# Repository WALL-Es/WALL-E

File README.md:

# WALL-E
-----------------------

----------------

## Description
A Full size Wall-E Clone from the movie WALL-E. With a ROS2+Gazebo Simulation. With Full CAD designs. 

## Featrues:
1. It will have a Simulation made with Gazebo.
2. Emulating the full motion of the real WALL-E.
3. Full PCB & 3D CAD designs.
4. Real Wall-E size.

### In V2:
- Autonomous motion
    - Adabting the Simulation using ROS2 Sensors
- Voice commanding & Sound system

## Photos:

### PCB:

### Schematic (See the [PDF](PCB/Schematic.pdf))
### 3D: 

### Simulation Demo:

https://github.com/user-attachments/assets/cbfe52af-3437-4783-bf1c-e89359c1bae6

## How to Build:

### 3D CAD:
1. Clone the Repo.
2. In the SW(Pack&Go) Directory, take the Wall-E.zip file and unzip it.
3. Open the main assembly in SolidWorks.
4. Edit whatever you want.
5. You can from there export to any format.
6. Enjoy.

### PCB:
1. Clone the Repo.
2. Open the PCB folder in Kicad.
3. Edit whateve you want.
4. That's it, Enjoy.

### Simulation:
1. Clone the Wall-E_Simulation Repo (You will find a shortcut in the GZ_simulation folder)
2. Make sure you have ROS2 Lyrical (Or any ROS2 Distro I believe) & Gazebo_Sim not Classic, installed on your linux machine.
3. Copy the package folder to your ROS2 Workspace.
4. Run `colcon build` and don't forget to source your workspace
5. Edit whatever you want.
6. Run `colcon build` again.
7. Run `ros2 launch wall-e_full gz_simulator_launch.py`
8. That's it, you will see gazebo launching and with your new changes.
9. Enjoyyy ❤️

# Build with ❤️ by @Nadoooor & @ZIZO932

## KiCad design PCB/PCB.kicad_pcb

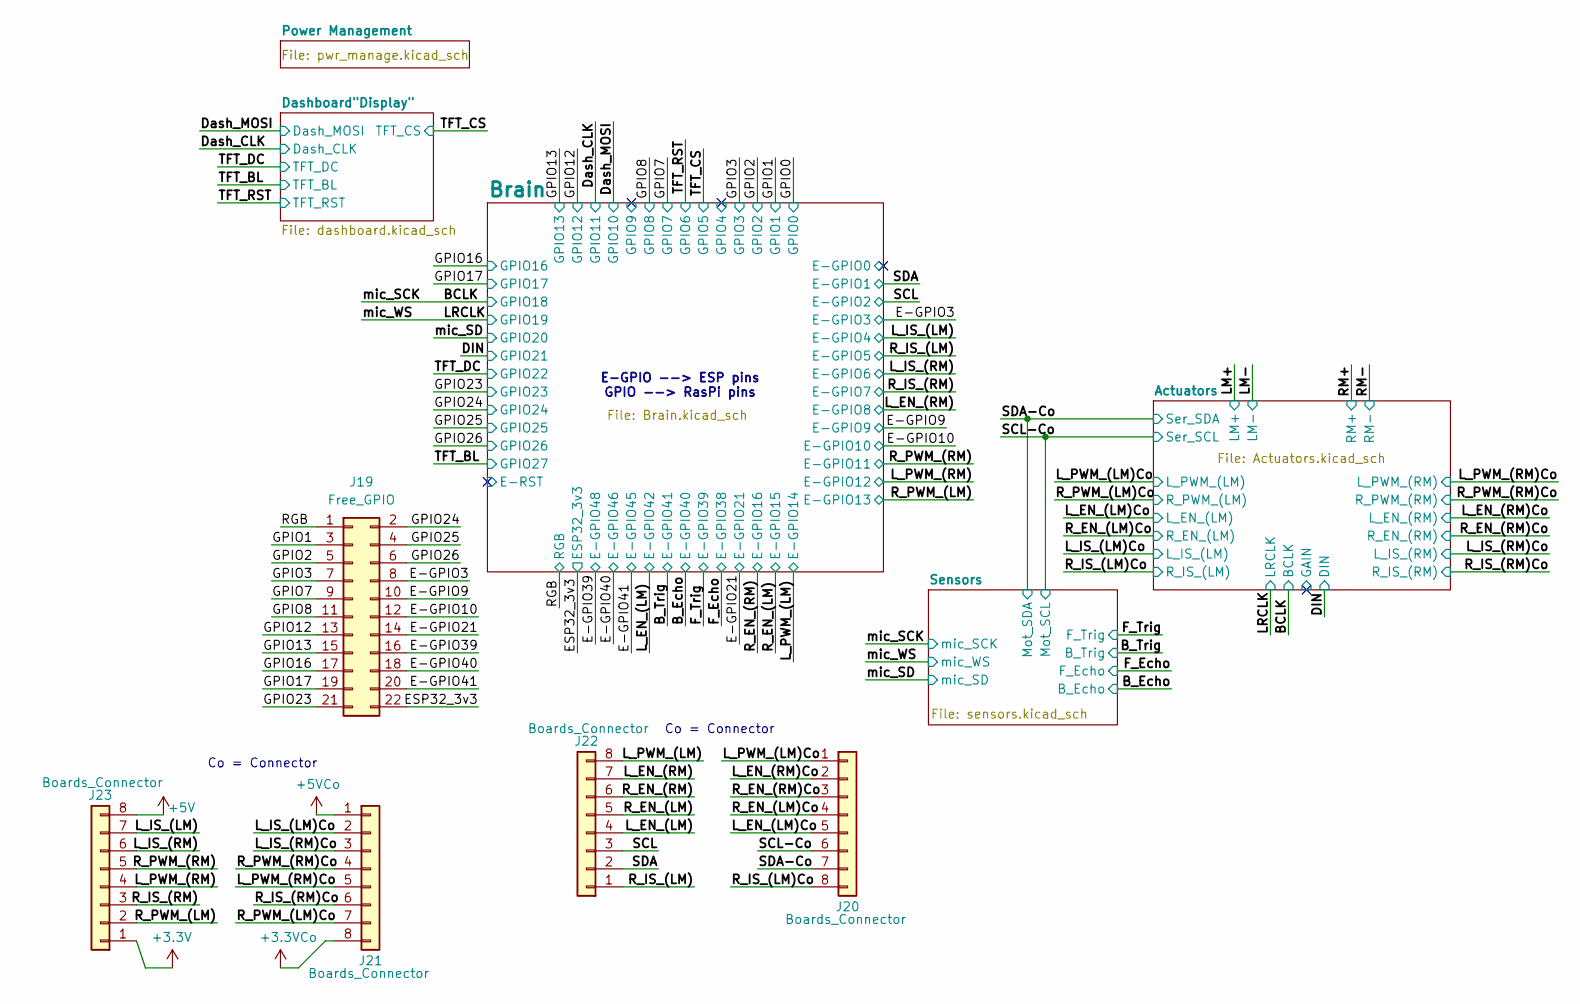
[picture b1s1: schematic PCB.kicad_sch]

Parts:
J19: Free_GPIO; PinHeader_2x11_P2.54mm_Vertical
J20, J21, J22, J23: Boards_Connector; JST_ZH_B8B-ZR-SM4-TF_1x08-1MP_P1.50mm_Vertical

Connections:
+3.3V: J19.22, J23.1; also elsewhere on the board
+3.3VCo: J21.8; also elsewhere on the board
+5V: J23.8; also elsewhere on the board
+5VCo: J21.1; also elsewhere on the board
/E-GPIO3: J19.8; also elsewhere on the board
/E-GPIO9: J19.10; also elsewhere on the board
/E-GPIO10: J19.12; also elsewhere on the board
/E-GPIO21: J19.14; also elsewhere on the board
/E-GPIO39: J19.16; also elsewhere on the board
/E-GPIO40: J19.18; also elsewhere on the board
/E-GPIO41: J19.20; also elsewhere on the board
/GPIO1: J19.3; also elsewhere on the board
/GPIO2: J19.5; also elsewhere on the board
/GPIO3: J19.7; also elsewhere on the board
/GPIO7: J19.9; also elsewhere on the board
/GPIO8: J19.11; also elsewhere on the board
/GPIO12: J19.13; also elsewhere on the board
/GPIO13: J19.15; also elsewhere on the board
/GPIO16: J19.17; also elsewhere on the board
/GPIO17: J19.19; also elsewhere on the board
/GPIO23: J19.21; also elsewhere on the board
/GPIO24: J19.2; also elsewhere on the board
/GPIO25: J19.4; also elsewhere on the board
/GPIO26: J19.6; also elsewhere on the board
/L_EN_(LM): J22.4; also elsewhere on the board
/L_EN_(LM)Co: J20.5; also elsewhere on the board
/L_EN_(RM): J22.7; also elsewhere on the board
/L_EN_(RM)Co: J20.2; also elsewhere on the board
/L_IS_(LM): J23.7; also elsewhere on the board
/L_IS_(LM)Co: J21.2; also elsewhere on the board
/L_IS_(RM): J23.6; also elsewhere on the board
/L_IS_(RM)Co: J21.3; also elsewhere on the board
/L_PWM_(LM): J22.8; also elsewhere on the board
/L_PWM_(LM)Co: J20.1; also elsewhere on the board
/L_PWM_(RM): J23.4; also elsewhere on the board
/L_PWM_(RM)Co: J21.5; also elsewhere on the board
/RGB: J19.1; also elsewhere on the board
/R_EN_(LM): J22.5; also elsewhere on the board
/R_EN_(LM)Co: J20.4; also elsewhere on the board
/R_EN_(RM): J22.6; also elsewhere on the board
/R_EN_(RM)Co: J20.3; also elsewhere on the board
/R_IS_(LM): J22.1; also elsewhere on the board
/R_IS_(LM)Co: J20.8; also elsewhere on the board
/R_IS_(RM): J23.3; also elsewhere on the board
/R_IS_(RM)Co: J21.6; also elsewhere on the board
/R_PWM_(LM): J23.2; also elsewhere on the board
/R_PWM_(LM)Co: J21.7; also elsewhere on the board
/R_PWM_(RM): J23.5; also elsewhere on the board
/R_PWM_(RM)Co: J21.4; also elsewhere on the board
/SCL: J22.3; also elsewhere on the board
/SCL-Co: J20.6; also elsewhere on the board
/SDA: J22.2; also elsewhere on the board
/SDA-Co: J20.7; also elsewhere on the board

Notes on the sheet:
Co = Connector
E-GPIO --> ESP pins GPIO --> RasPi pins

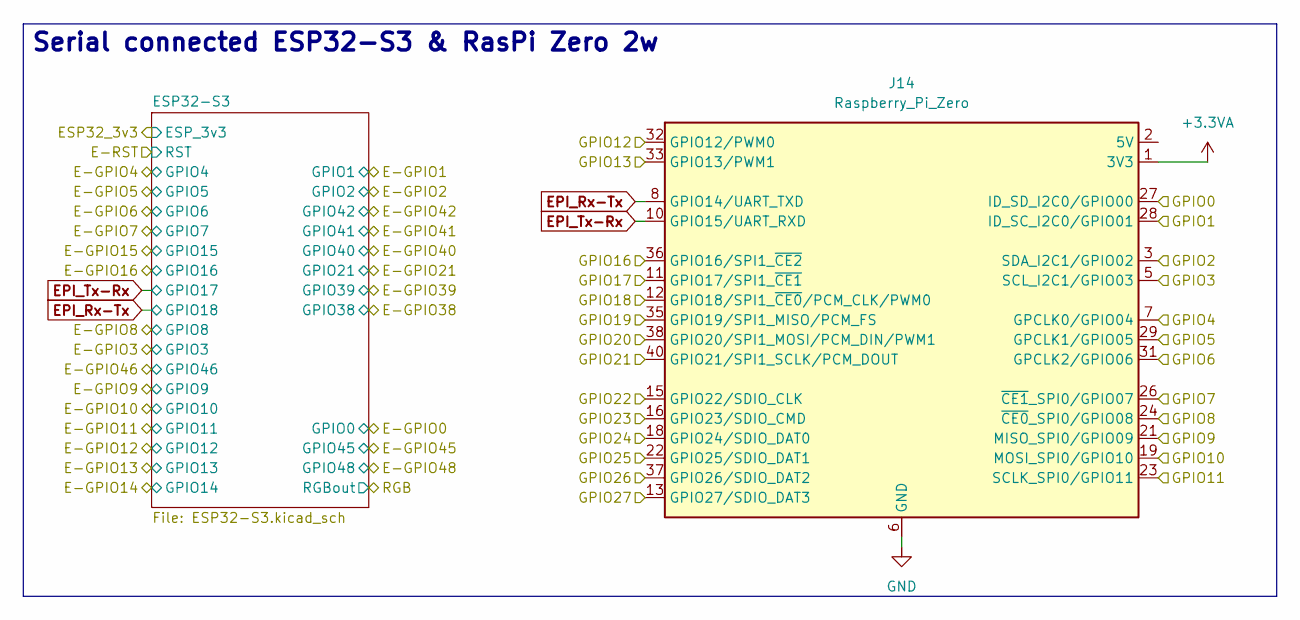
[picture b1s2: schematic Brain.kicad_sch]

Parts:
J14: Raspberry_Pi_Zero; MODULE_RASPBERRY_PI_ZERO_2_W

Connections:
+3.3VA: J14.1 (3V3), J14.17 (3V3)
/BCLK: J14.12 (GPIO18/SPI1_~CE0/PCM_CLK/PWM0); also elsewhere on the board
/Brain/GPIO4: J14.7 (GPCLK0/GPIO04)
/Brain/GPIO9: J14.21 (MISO_SPI0/GPIO09)
/DIN: J14.40 (GPIO21/SPI1_SCLK/PCM_DOUT); also elsewhere on the board
/Dash_CLK: J14.23 (SCLK_SPI0/GPIO11); also elsewhere on the board
/Dash_MOSI: J14.19 (MOSI_SPI0/GPIO10); also elsewhere on the board
/GPIO0: J14.27 (ID_SD_I2C0/GPIO00)
/GPIO1: J14.28 (ID_SC_I2C0/GPIO01); also elsewhere on the board
/GPIO2: J14.3 (SDA_I2C1/GPIO02); also elsewhere on the board
/GPIO3: J14.5 (SCL_I2C1/GPIO03); also elsewhere on the board
/GPIO7: J14.26 (~CE1_SPI0/GPIO07); also elsewhere on the board
/GPIO8: J14.24 (~CE0_SPI0/GPIO08); also elsewhere on the board
/GPIO12: J14.32 (GPIO12/PWM0); also elsewhere on the board
/GPIO13: J14.33 (GPIO13/PWM1); also elsewhere on the board
/GPIO16: J14.36 (GPIO16/SPI1_~CE2); also elsewhere on the board
/GPIO17: J14.11 (GPIO17/SPI1_~CE1); also elsewhere on the board
/GPIO23: J14.16 (GPIO23/SDIO_CMD); also elsewhere on the board
/GPIO24: J14.18 (GPIO24/SDIO_DAT0); also elsewhere on the board
/GPIO25: J14.22 (GPIO25/SDIO_DAT1); also elsewhere on the board
/GPIO26: J14.37 (GPIO26/SDIO_DAT2); also elsewhere on the board
/LRCLK: J14.35 (GPIO19/SPI1_MISO/PCM_FS); also elsewhere on the board
/TFT_BL: J14.13 (GPIO27/SDIO_DAT3); also elsewhere on the board
/TFT_CS: J14.29 (GPCLK1/GPIO05); also elsewhere on the board
/TFT_DC: J14.15 (GPIO22/SDIO_CLK); also elsewhere on the board
/TFT_RST: J14.31 (GPCLK2/GPIO06); also elsewhere on the board
/mic_SD: J14.38 (GPIO20/SPI1_MOSI/PCM_DIN/PWM1); also elsewhere on the board
EPI_Rx-Tx: J14.8 (GPIO14/UART_TXD); also elsewhere on the board
EPI_Tx-Rx: J14.10 (GPIO15/UART_RXD); also elsewhere on the board
GND: J14.6 (GND), J14.9 (GND), J14.14 (GND), J14.20 (GND), J14.25 (GND), J14.30 (GND), J14.34 (GND), J14.39 (GND); also elsewhere on the board
unnamed: J14.2 (5V), J14.4 (5V)

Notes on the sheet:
Serial connected ESP32-S3 & RasPi Zero 2w

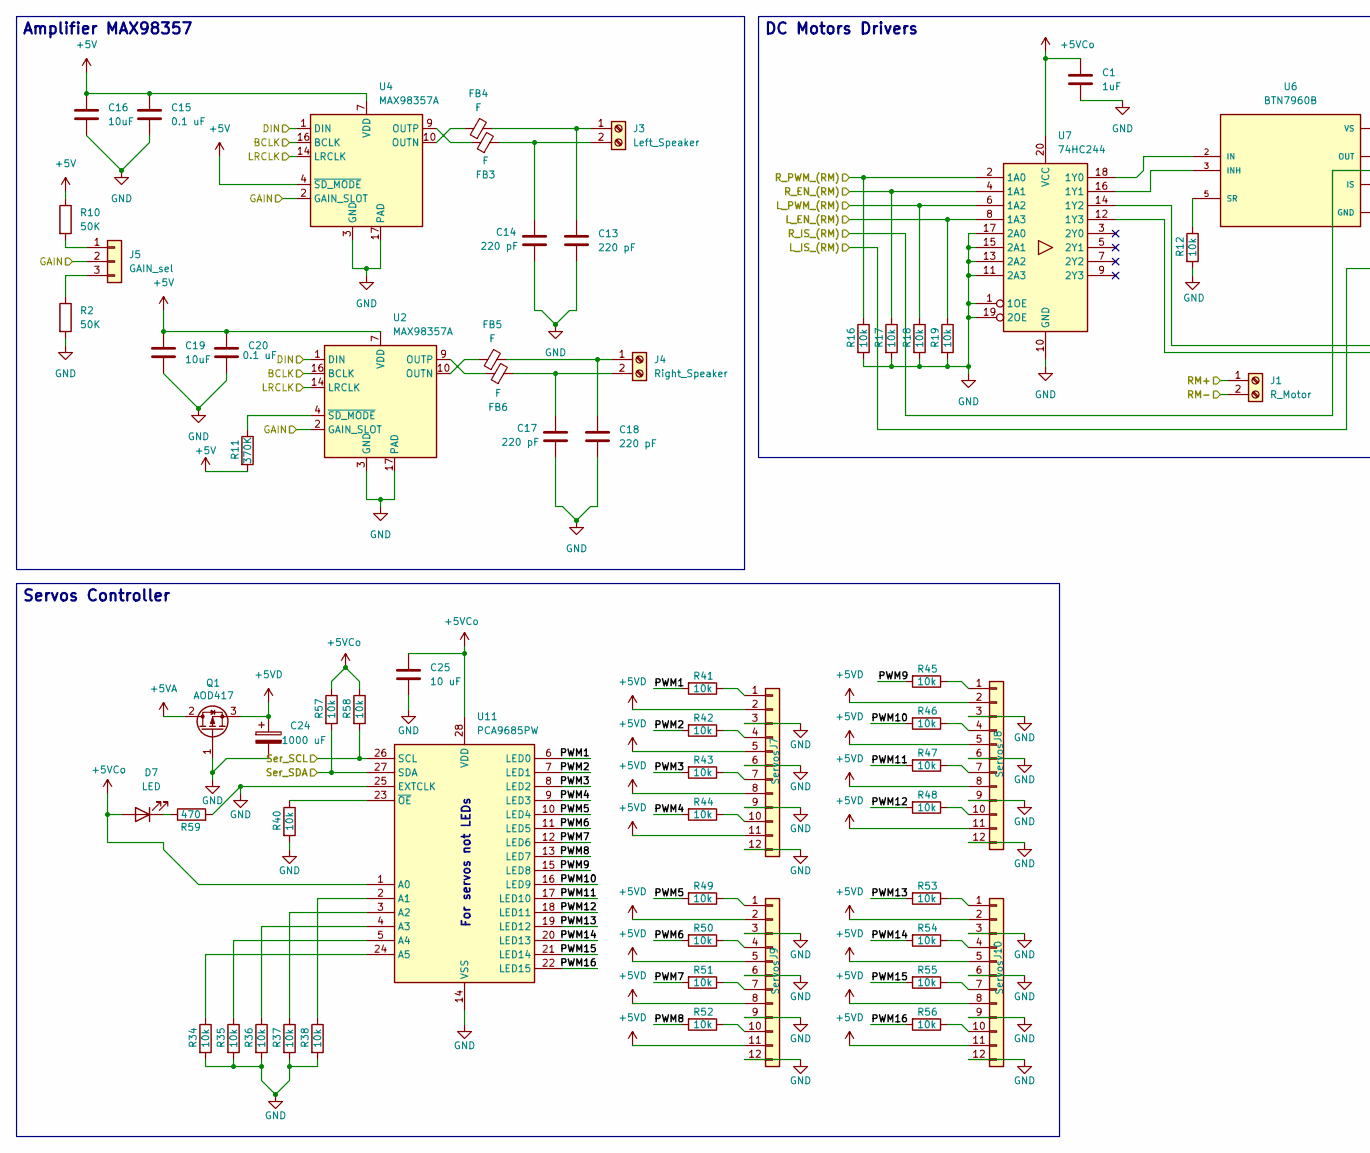
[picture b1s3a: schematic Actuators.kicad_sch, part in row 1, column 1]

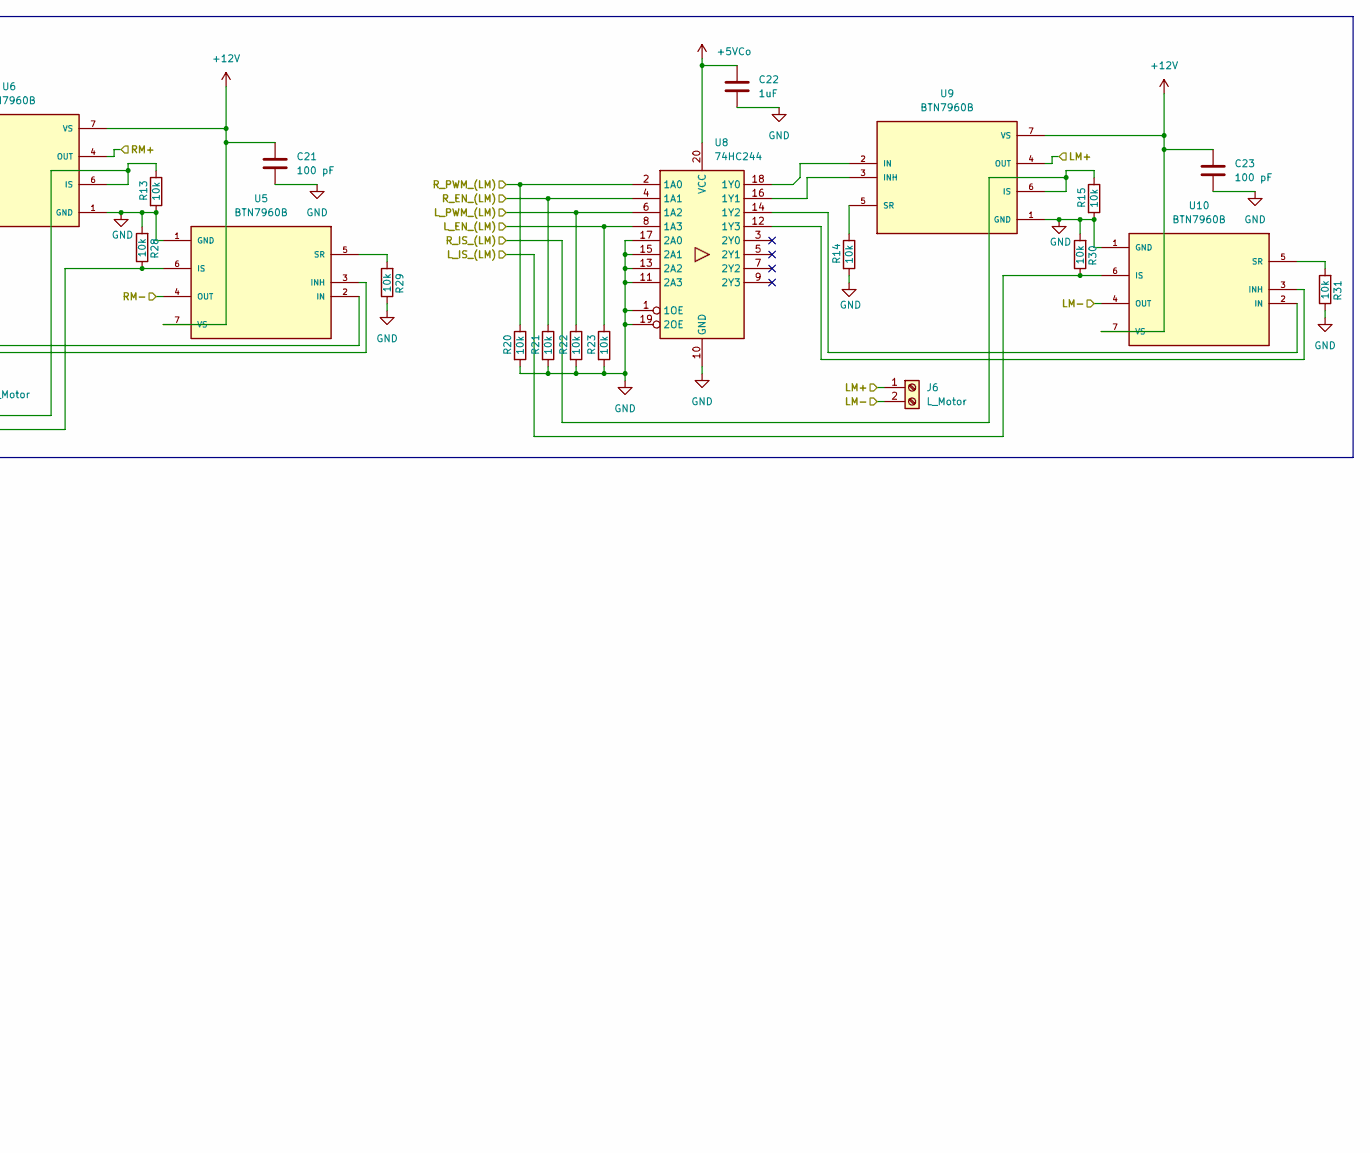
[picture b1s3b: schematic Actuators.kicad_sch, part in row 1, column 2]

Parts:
C1, C22: 1uF; C_0603_1608Metric_Pad1.08x0.95mm_HandSolder
C13, C14, C17, C18: 220 pF; C_0603_1608Metric_Pad1.08x0.95mm_HandSolder
C15, C20: 0.1 uF; C_0603_1608Metric_Pad1.08x0.95mm_HandSolder
C16, C19: 10uF; C_0603_1608Metric_Pad1.08x0.95mm_HandSolder
C21, C23: 100 pF; C_0603_1608Metric_Pad1.08x0.95mm_HandSolder
C24: 1000 uF; CP_Radial_D8.0mm_P2.50mm
C25: 10 uF; C_0603_1608Metric_Pad1.08x0.95mm_HandSolder
D7: LED; LED_0603_1608Metric_Pad1.05x0.95mm_HandSolder
FB3, FB4, FB5, FB6: F; C_0603_1608Metric_Pad1.08x0.95mm_HandSolder
J1: R_Motor; Altech_AK100_1x02_P5.00mm
J3: Left_Speaker; JST_ZH_B2B-ZR-SM4-TF_1x02-1MP_P1.50mm_Vertical
J4: Right_Speaker; JST_ZH_B2B-ZR-SM4-TF_1x02-1MP_P1.50mm_Vertical
J5: GAIN_sel; SolderJumper-3_P1.3mm_Open_Pad1.0x1.5mm
J6: L_Motor; Altech_AK100_1x02_P5.00mm
J7, J8, J9, J10: Servos; Free_GPIO_FP
Q1: AOD417; TO-252-3_TabPin2
R2, R10: 50K; R_0603_1608Metric_Pad0.98x0.95mm_HandSolder
R11: 370K; R_0603_1608Metric_Pad0.98x0.95mm_HandSolder
R12, R13, R14, R15, R16, R17, R18, R19, R20, R21, R22, R23, R28, R29, R30, R31, R34, R35, R36, R37, R38, R40, R41, R42, R43, R44, R45, R46, R47, R48, R49, R50, R51, R52, R53, R54, R55, R56, R57, R58: 10k; R_0603_1608Metric_Pad0.98x0.95mm_HandSolder
R59: 470; R_0603_1608Metric_Pad0.98x0.95mm_HandSolder
U2, U4: MAX98357A; TQFN-16-1EP_3x3mm_P0.5mm_EP1.23x1.23mm
U5, U6, U9, U10: BTN7960B; IC_BTN7960B; PARTREV 1.0
U7, U8: 74HC244; TSSOP-20_4.4x6.5mm_P0.65mm
U11: PCA9685PW; TSSOP-28_4.4x9.7mm_P0.65mm

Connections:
+5V: C15.2, C16.2, C19.2, C20.2, R10.1, R11.2, U2.7 (VDD), U2.8 (VDD), U4.4 (~SD_MODE), U4.7 (VDD), U4.8 (VDD); also elsewhere on the board
+5VA: Q1.2 (D); also elsewhere on the board
+5VCo: C1.1, C22.1, C25.1, D7.2 (A), R57.1, R58.1, U7.20 (VCC), U8.20 (VCC), U11.1 (A0), U11.28 (VDD); also elsewhere on the board
+5VD: C24.1, J7.2, J7.5, J7.8, J7.11, J8.2, J8.5, J8.8, J8.11, J9.2, J9.5, J9.8, J9.11, J10.2, J10.5, J10.8, J10.11, Q1.3 (S)
+12V: C21.1, C23.1, U5.7 (VS), U6.7 (VS), U9.7 (VS), U10.7 (VS); also elsewhere on the board
/Actuators/GAIN: J5.2, U2.2 (GAIN_SLOT), U4.2 (GAIN_SLOT)
/Actuators/PWM1: R41.2, U11.6 (LED0)
/Actuators/PWM2: R42.2, U11.7 (LED1)
/Actuators/PWM3: R43.2, U11.8 (LED2)
/Actuators/PWM4: R44.2, U11.9 (LED3)
/Actuators/PWM5: R49.2, U11.10 (LED4)
/Actuators/PWM6: R50.2, U11.11 (LED5)
/Actuators/PWM7: R51.2, U11.12 (LED6)
/Actuators/PWM8: R52.2, U11.13 (LED7)
/Actuators/PWM9: R45.2, U11.15 (LED8)
/Actuators/PWM10: R46.2, U11.16 (LED9)
/Actuators/PWM11: R47.2, U11.17 (LED10)
/Actuators/PWM12: R48.2, U11.18 (LED11)
/Actuators/PWM13: R53.2, U11.19 (LED12)
/Actuators/PWM14: R54.2, U11.20 (LED13)
/Actuators/PWM15: R55.2, U11.21 (LED14)
/Actuators/PWM16: R56.2, U11.22 (LED15)
/BCLK: U2.16 (BCLK), U4.16 (BCLK); also elsewhere on the board
/DIN: U2.1 (DIN), U4.1 (DIN); also elsewhere on the board
/LM+: J6.1, U9.4 (OUT), U9.8 (OUT)
/LM-: J6.2, U10.4 (OUT), U10.8 (OUT)
/LRCLK: U2.14 (LRCLK), U4.14 (LRCLK); also elsewhere on the board
/L_EN_(LM)Co: R23.1, U8.8 (1A3); also elsewhere on the board
/L_EN_(RM)Co: R19.1, U7.8 (1A3); also elsewhere on the board
/L_IS_(LM)Co: R30.1, U10.6 (IS); also elsewhere on the board
/L_IS_(RM)Co: R28.1, U5.6 (IS); also elsewhere on the board
/L_PWM_(LM)Co: R22.1, U8.6 (1A2); also elsewhere on the board
/L_PWM_(RM)Co: R18.1, U7.6 (1A2); also elsewhere on the board
/RM+: J1.1, U6.4 (OUT), U6.8 (OUT)
/RM-: J1.2, U5.4 (OUT), U5.8 (OUT)
/R_EN_(LM)Co: R21.1, U8.4 (1A1); also elsewhere on the board
/R_EN_(RM)Co: R17.1, U7.4 (1A1); also elsewhere on the board
/R_IS_(LM)Co: R15.1, U9.6 (IS); also elsewhere on the board
/R_IS_(RM)Co: R13.1, U6.6 (IS); also elsewhere on the board
/R_PWM_(LM)Co: R20.1, U8.2 (1A0); also elsewhere on the board
/R_PWM_(RM)Co: R16.1, U7.2 (1A0); also elsewhere on the board
/SCL-Co: R58.2, U11.26 (SCL); also elsewhere on the board
/SDA-Co: R57.2, U11.27 (SDA); also elsewhere on the board
GND: C1.2, C13.1, C14.1, C15.1, C16.1, C17.1, C18.1, C19.1, C20.1, C21.2, C22.2, C23.2, C24.2, C25.2, J7.3, J7.6, J7.9, J7.12, J8.3, J8.6, J8.9, J8.12, J9.3, J9.6, J9.9, J9.12, J10.3, J10.6, J10.9, J10.12, Q1.1 (G), R2.2, R12.2, R13.2, R14.2, R15.2, R16.2, R17.2, R18.2, R19.2, R20.2, R21.2, R22.2, R23.2, R28.2, R29.1, R30.2, R31.1, R34.2, R35.2, R36.2, R37.2, R38.2, R40.2, R59.2, U2.3 (GND), U2.11 (GND), U2.15 (GND), U2.17 (PAD), U4.3 (GND), U4.11 (GND), U4.15 (GND), U4.17 (PAD), U5.1 (GND), U6.1 (GND), U7.1 (1OE), U7.10 (GND), U7.11 (2A3), U7.13 (2A2), U7.15 (2A1), U7.17 (2A0), U7.19 (2OE), U8.1 (1OE), U8.10 (GND), U8.11 (2A3), U8.13 (2A2), U8.15 (2A1), U8.17 (2A0), U8.19 (2OE), U9.1 (GND), U10.1 (GND), U11.14 (VSS), U11.25 (EXTCLK); also elsewhere on the board
unnamed: D7.1 (K), R59.1
unnamed: C13.2, FB4.2, J3.1
unnamed: C14.2, FB3.2, J3.2
unnamed: C18.2, FB5.2, J4.1
unnamed: C17.2, FB6.2, J4.2
unnamed: J5.1, R10.2
unnamed: J5.3, R2.1
unnamed: J7.1, R41.1
unnamed: J7.4, R42.1
unnamed: J7.7, R43.1
unnamed: J7.10, R44.1
unnamed: J8.1, R45.1
unnamed: J8.4, R46.1
unnamed: J8.7, R47.1
unnamed: J8.10, R48.1
unnamed: J9.1, R49.1
unnamed: J9.4, R50.1
unnamed: J9.7, R51.1
unnamed: J9.10, R52.1
unnamed: J10.1, R53.1
unnamed: J10.4, R54.1
unnamed: J10.7, R55.1
unnamed: J10.10, R56.1
unnamed: FB5.1, U2.10 (OUTN)
unnamed: FB6.1, U2.9 (OUTP)
unnamed: R11.1, U2.4 (~SD_MODE)
unnamed: FB4.1, U4.10 (OUTN)
unnamed: FB3.1, U4.9 (OUTP)
unnamed: U5.2 (IN), U7.14 (1Y2)
unnamed: U5.3 (INH), U7.12 (1Y3)
unnamed: R29.2, U5.5 (SR)
unnamed: U6.2 (IN), U7.18 (1Y0)
unnamed: U6.3 (INH), U7.16 (1Y1)
unnamed: R12.1, U6.5 (SR)
unnamed: U8.18 (1Y0), U9.2 (IN)
unnamed: U8.16 (1Y1), U9.3 (INH)
unnamed: R14.1, U9.5 (SR)
unnamed: U8.14 (1Y2), U10.2 (IN)
unnamed: U8.12 (1Y3), U10.3 (INH)
unnamed: R31.2, U10.5 (SR)
unnamed: R38.1, U11.2 (A1)
unnamed: R37.1, U11.3 (A2)
unnamed: R36.1, U11.4 (A3)
unnamed: R35.1, U11.5 (A4)
unnamed: R34.1, U11.24 (A5)
unnamed: R40.1, U11.23 (~OE)

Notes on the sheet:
For servos not LEDs
Amplifier MAX98357
DC Motors Drivers
Servos Controller

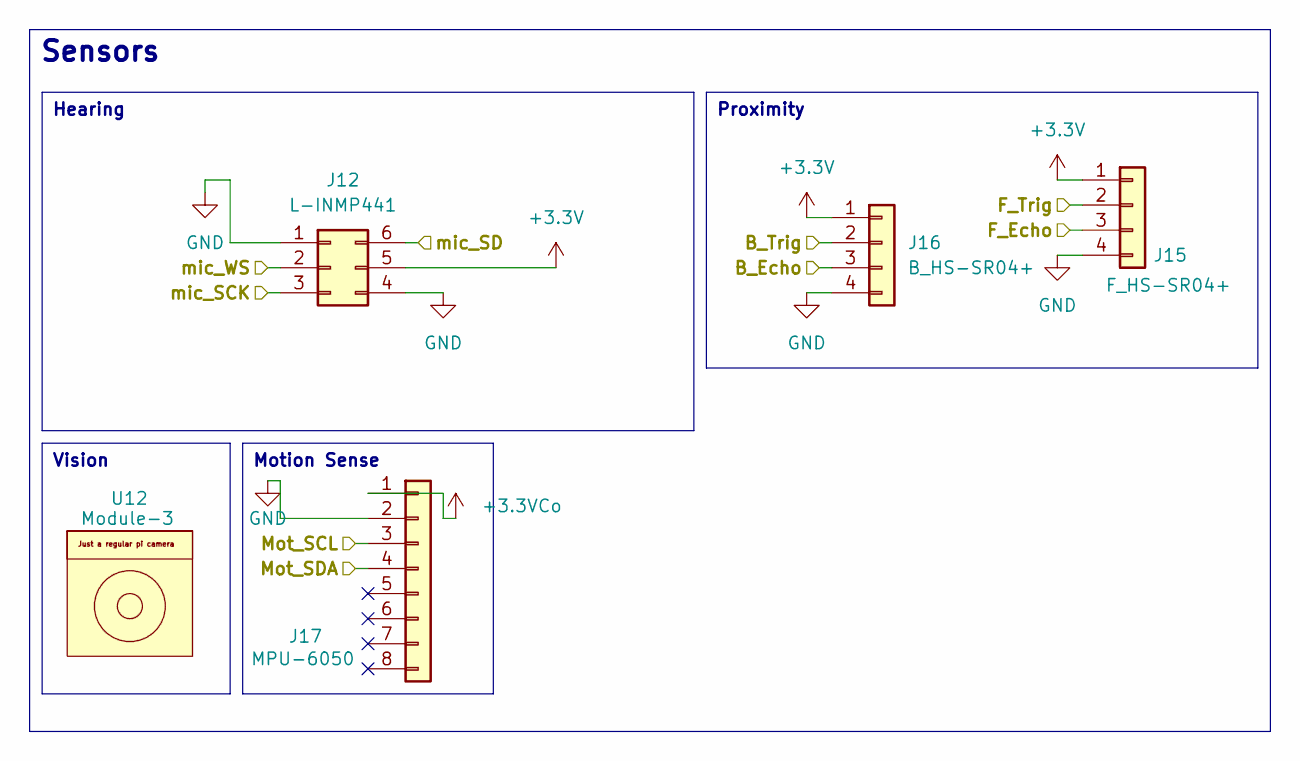
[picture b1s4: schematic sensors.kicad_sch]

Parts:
J12: L-INMP441; JST_ZH_B6B-ZR-SM4-TF_1x06-1MP_P1.50mm_Vertical
J15: F_HS-SR04+; JST_ZH_B4B-ZR-SM4-TF_1x04-1MP_P1.50mm_Vertical
J16: B_HS-SR04+; JST_ZH_B4B-ZR-SM4-TF_1x04-1MP_P1.50mm_Vertical
J17: MPU-6050; JST_ZH_B8B-ZR-SM4-TF_1x08-1MP_P1.50mm_Vertical
U12: Module-3

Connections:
+3.3V: J12.5, J15.1, J16.1; also elsewhere on the board
+3.3VCo: J17.1; also elsewhere on the board
/BCLK: J12.3; also elsewhere on the board
/B_Echo: J16.3; also elsewhere on the board
/B_Trig: J16.2; also elsewhere on the board
/F_Echo: J15.3; also elsewhere on the board
/F_Trig: J15.2; also elsewhere on the board
/LRCLK: J12.2; also elsewhere on the board
/SCL-Co: J17.3; also elsewhere on the board
/SDA-Co: J17.4; also elsewhere on the board
/mic_SD: J12.6; also elsewhere on the board
GND: J12.1, J12.4, J15.4, J16.4, J17.2; also elsewhere on the board

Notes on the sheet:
Sensors
Motion Sense
Proximity
Vision
Hearing

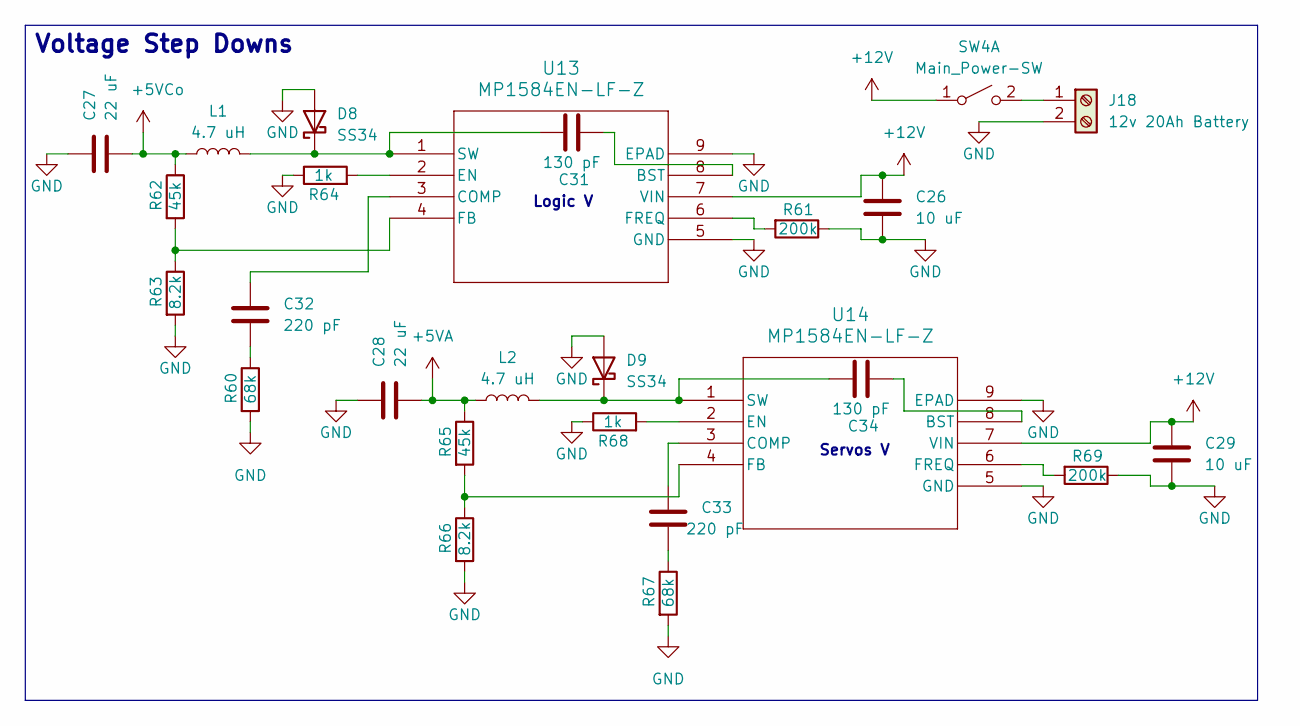
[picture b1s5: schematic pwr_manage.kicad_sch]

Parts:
C26, C29: 10 uF; C_0603_1608Metric_Pad1.08x0.95mm_HandSolder
C27, C28: 22 uF; C_0603_1608Metric_Pad1.08x0.95mm_HandSolder
C31, C34: 130 pF; C_0603_1608Metric_Pad1.08x0.95mm_HandSolder
C32, C33: 220 pF; C_0603_1608Metric_Pad1.08x0.95mm_HandSolder
D8, D9: SS34; D_SMA
J18: 12v 20Ah Battery; BarrelJack_Horizontal
L1, L2: 4.7 uH; L_0603_1608Metric_Pad1.05x0.95mm_HandSolder
R60, R67: 68k; R_0603_1608Metric_Pad0.98x0.95mm_HandSolder
R61, R69: 200k; R_0603_1608Metric_Pad0.98x0.95mm_HandSolder
R62, R65: 45k; R_0603_1608Metric_Pad0.98x0.95mm_HandSolder
R63, R66: 8.2k; R_0603_1608Metric_Pad0.98x0.95mm_HandSolder
R64, R68: 1k; R_0603_1608Metric_Pad0.98x0.95mm_HandSolder
SW4: Main_Power-SW; JST_PH_B2B-PH-K_1x02_P2.00mm_Vertical
U13, U14: MP1584EN-LF-Z; SOIC12

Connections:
+5VA: C28.2, L2.1, R65.1; also elsewhere on the board
+5VCo: C27.2, L1.1, R62.1; also elsewhere on the board
+12V: C26.1, C29.1, SW4.1 (A), U13.7 (VIN), U14.7 (VIN); also elsewhere on the board
GND: C26.2, C27.1, C28.1, C29.2, D8.2 (A), D9.2 (A), J18.2, R60.2, R61.1, R63.2, R64.1, R66.2, R67.2, R68.1, R69.1, U13.5 (GND), U13.9 (EPAD), U14.5 (GND), U14.9 (EPAD); also elsewhere on the board
unnamed: C32.2, R60.1
unnamed: C33.2, R67.1
unnamed: C31.2, D8.1 (K), L1.2, U13.1 (SW)
unnamed: C34.2, D9.1 (K), L2.2, U14.1 (SW)
unnamed: J18.1, SW4.2 (B)
unnamed: C31.1, U13.8 (BST)
unnamed: C32.1, U13.3 (COMP)
unnamed: R64.2, U13.2 (EN)
unnamed: R62.2, R63.1, U13.4 (FB)
unnamed: R61.2, U13.6 (FREQ)
unnamed: C34.1, U14.8 (BST)
unnamed: C33.1, U14.3 (COMP)
unnamed: R68.2, U14.2 (EN)
unnamed: R65.2, R66.1, U14.4 (FB)
unnamed: R69.2, U14.6 (FREQ)

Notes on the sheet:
Servos V
Logic V
Voltage Step Downs

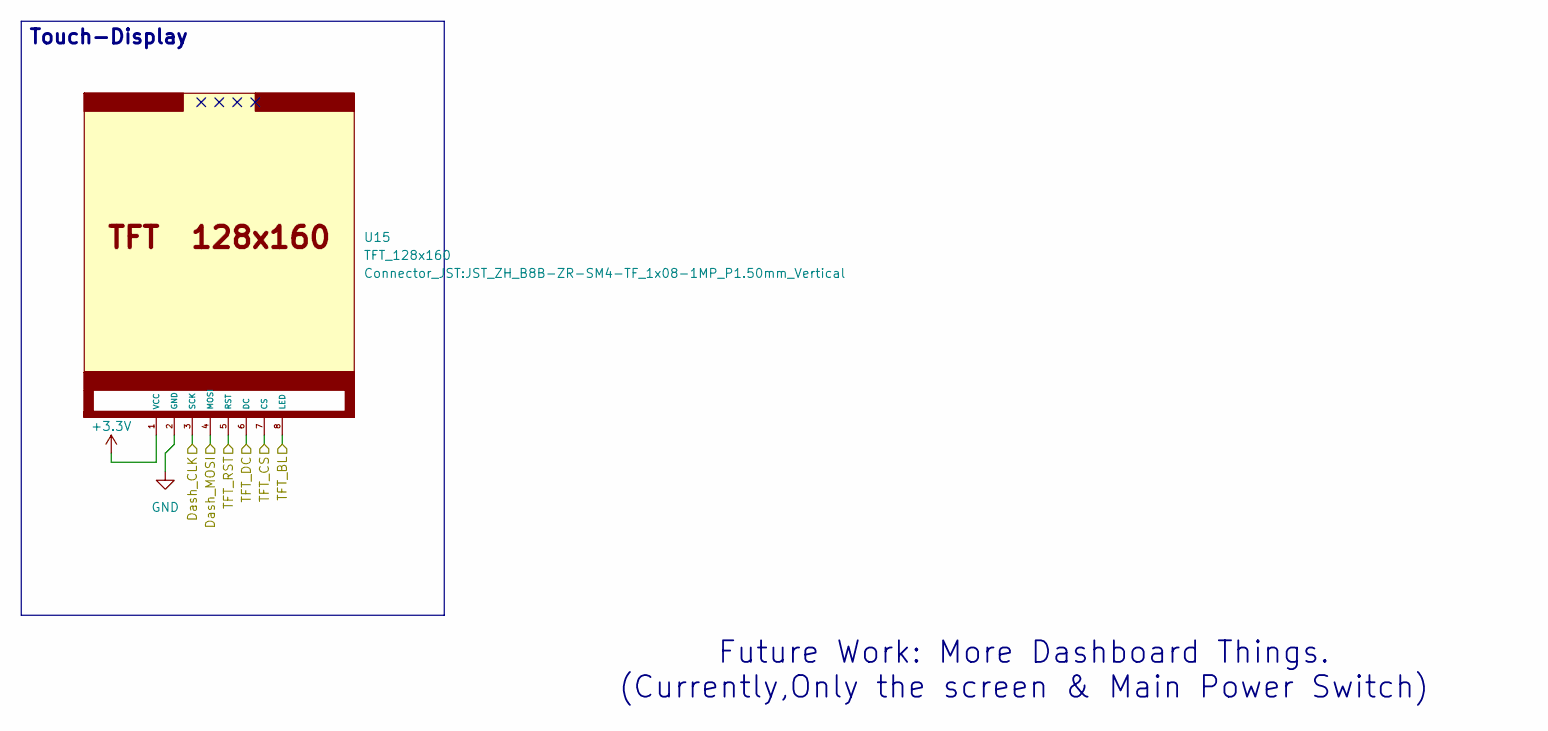
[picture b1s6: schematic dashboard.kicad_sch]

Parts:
U15: TFT_128x160; JST_ZH_B8B-ZR-SM4-TF_1x08-1MP_P1.50mm_Vertical

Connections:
+3.3V: U15.1 (VCC); also elsewhere on the board
/Dash_CLK: U15.3 (SCK); also elsewhere on the board
/Dash_MOSI: U15.4 (MOSI); also elsewhere on the board
/TFT_BL: U15.8 (LED); also elsewhere on the board
/TFT_CS: U15.7 (CS); also elsewhere on the board
/TFT_DC: U15.6 (DC); also elsewhere on the board
/TFT_RST: U15.5 (RST); also elsewhere on the board
GND: U15.2 (GND); also elsewhere on the board

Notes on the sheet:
Future Work: More Dashboard Things. (Currently,Only the screen & Main Power Switch)
Touch-Display

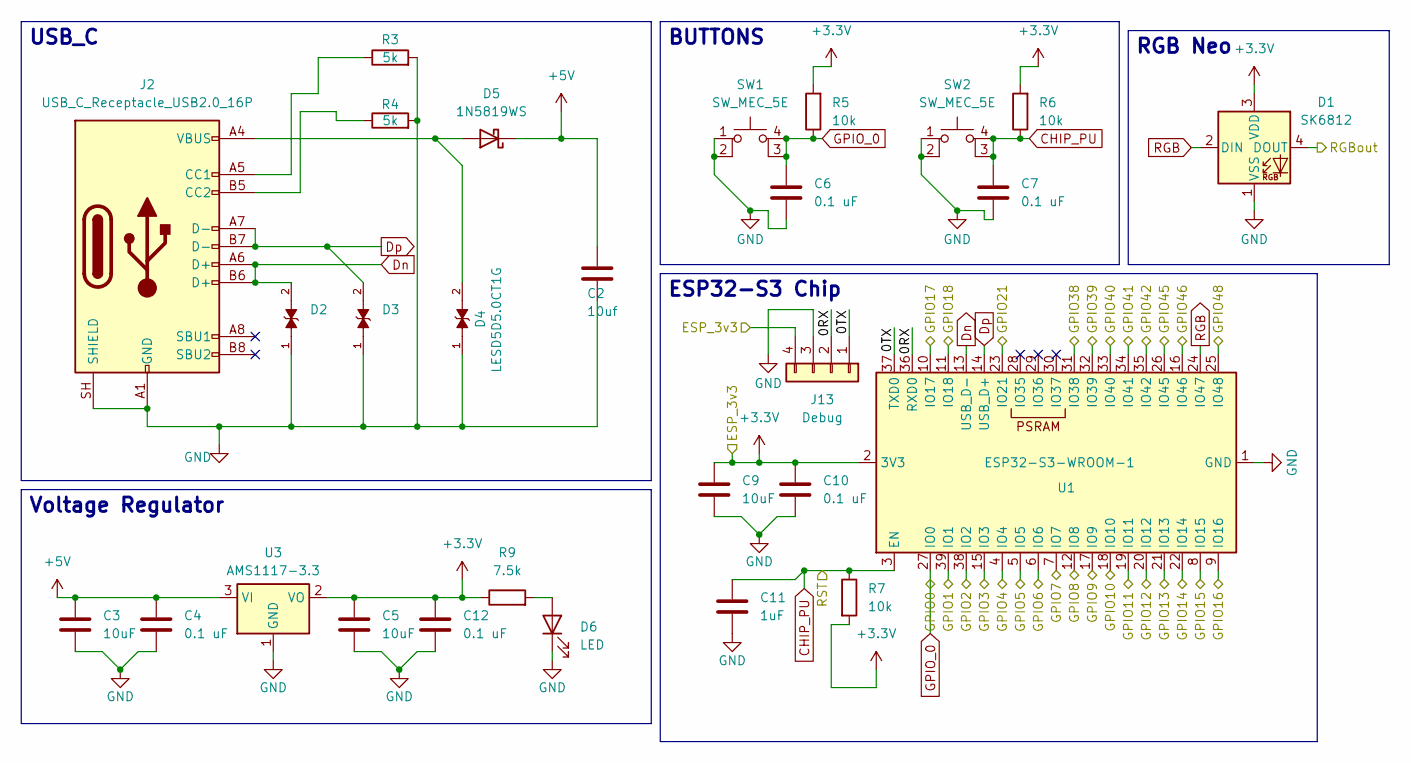
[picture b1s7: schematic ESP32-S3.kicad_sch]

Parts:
C2: 10uf; C_0603_1608Metric_Pad1.08x0.95mm_HandSolder
C3, C5, C9: 10uF; C_0603_1608Metric_Pad1.08x0.95mm_HandSolder
C4, C6, C7, C10, C12: 0.1 uF; C_0603_1608Metric_Pad1.08x0.95mm_HandSolder
C11: 1uF; C_0603_1608Metric_Pad1.08x0.95mm_HandSolder
D1: SK6812; LED_SK6812_PLCC4_5.0x5.0mm_P3.2mm
D2, D3, D4: LESD5D5.0CT1G; TVS_LESD5D5.0CT1G; PARTREV O
D5: 1N5819WS; D_SOD-323
D6: LED; LED_0603_1608Metric_Pad1.05x0.95mm_HandSolder
J2: USB_C_Receptacle_USB2.0_16P; USB_C_Receptacle_Amphenol_12401610E4-2A_CircularHoles
J13: Debug; JST_ZH_B4B-ZR-SM4-TF_1x04-1MP_P1.50mm_Vertical
R3, R4: 5k; R_0603_1608Metric_Pad0.98x0.95mm_HandSolder
R5, R6, R7: 10k; R_0603_1608Metric_Pad0.98x0.95mm_HandSolder
R9: 7.5k; R_0603_1608Metric_Pad0.98x0.95mm_HandSolder
SW1, SW2: SW_MEC_5E; SW_Push_1P1T_NO_CK_KMR2
U1: ESP32-S3-WROOM-1
U3: AMS1117-3.3; SOT-223-3_TabPin2

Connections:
+3.3V: C5.1, C9.1, C10.1, C12.1, D1.3 (VDD), J13.4, R5.2, R6.2, R7.2, R9.1, U1.2 (3V3), U3.2 (VO); also elsewhere on the board
+5V: C2.1, C3.1, C4.1, D5.1 (K), U3.3 (VI); also elsewhere on the board
/B_Echo: U1.33 (IO40); also elsewhere on the board
/B_Trig: U1.34 (IO41); also elsewhere on the board
/Brain/ESP32-S3/0RX: J13.2, U1.36 (RXD0)
/Brain/ESP32-S3/0TX: J13.1, U1.37 (TXD0)
/E-GPIO3: U1.15 (IO3); also elsewhere on the board
/E-GPIO9: U1.17 (IO9); also elsewhere on the board
/E-GPIO10: U1.18 (IO10); also elsewhere on the board
/E-GPIO21: U1.23 (IO21); also elsewhere on the board
/E-GPIO39: U1.25 (IO48); also elsewhere on the board
/E-GPIO40: U1.16 (IO46); also elsewhere on the board
/E-GPIO41: U1.26 (IO45); also elsewhere on the board
/F_Echo: U1.31 (IO38); also elsewhere on the board
/F_Trig: U1.32 (IO39); also elsewhere on the board
/L_EN_(LM): U1.35 (IO42); also elsewhere on the board
/L_EN_(RM): U1.12 (IO8); also elsewhere on the board
/L_IS_(LM): U1.4 (IO4); also elsewhere on the board
/L_IS_(RM): U1.6 (IO6); also elsewhere on the board
/L_PWM_(LM): U1.22 (IO14); also elsewhere on the board
/L_PWM_(RM): U1.20 (IO12); also elsewhere on the board
/RGB: D1.4 (DOUT); also elsewhere on the board
/R_EN_(LM): U1.8 (IO15); also elsewhere on the board
/R_EN_(RM): U1.9 (IO16); also elsewhere on the board
/R_IS_(LM): U1.5 (IO5); also elsewhere on the board
/R_IS_(RM): U1.7 (IO7); also elsewhere on the board
/R_PWM_(LM): U1.21 (IO13); also elsewhere on the board
/R_PWM_(RM): U1.19 (IO11); also elsewhere on the board
/SCL: U1.38 (IO2); also elsewhere on the board
/SDA: U1.39 (IO1); also elsewhere on the board
CHIP_PU: C7.1, C11.1, R6.1, R7.1, SW2.3 (K), SW2.4 (A), U1.3 (EN)
Dn: D2.2, J2.A6 (D+), J2.B6 (D+), U1.13 (USB_D-)
Dp: D3.2, J2.A7 (D-), J2.B7 (D-), U1.14 (USB_D+)
EPI_Rx-Tx: U1.11 (IO18); also elsewhere on the board
EPI_Tx-Rx: U1.10 (IO17); also elsewhere on the board
GND: C2.2, C3.2, C4.2, C5.2, C6.2, C7.2, C9.2, C10.2, C11.2, C12.2, D1.1 (VSS), D2.1, D3.1, D4.1, D6.1 (K), J2.A1 (GND), J2.A12 (GND), J2.B1 (GND), J2.B12 (GND), J2.SH (SHIELD), J13.3, R3.2, R4.2, SW1.1, SW1.2, SW2.1, SW2.2, U1.1 (GND), U1.40 (GND), U1.41 (GND), U3.1 (GND); also elsewhere on the board
GPIO_0: C6.1, R5.1, SW1.3 (K), SW1.4 (A), U1.27 (IO0)
unnamed: D4.2, D5.2 (A), J2.A4 (VBUS), J2.A9 (VBUS), J2.B4 (VBUS), J2.B9 (VBUS)
unnamed: D6.2 (A), R9.2
unnamed: J2.A5 (CC1), R3.1
unnamed: J2.B5 (CC2), R4.1
RGB: D1.2 (DIN), U1.24 (IO47)

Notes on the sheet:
BUTTONS
RGB Neo
Voltage Regulator
ESP32-S3 Chip
USB_C
